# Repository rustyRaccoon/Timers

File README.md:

# Timers
 Vairous timer circuits, e.g. variable frequency, variable duty cycle, ...

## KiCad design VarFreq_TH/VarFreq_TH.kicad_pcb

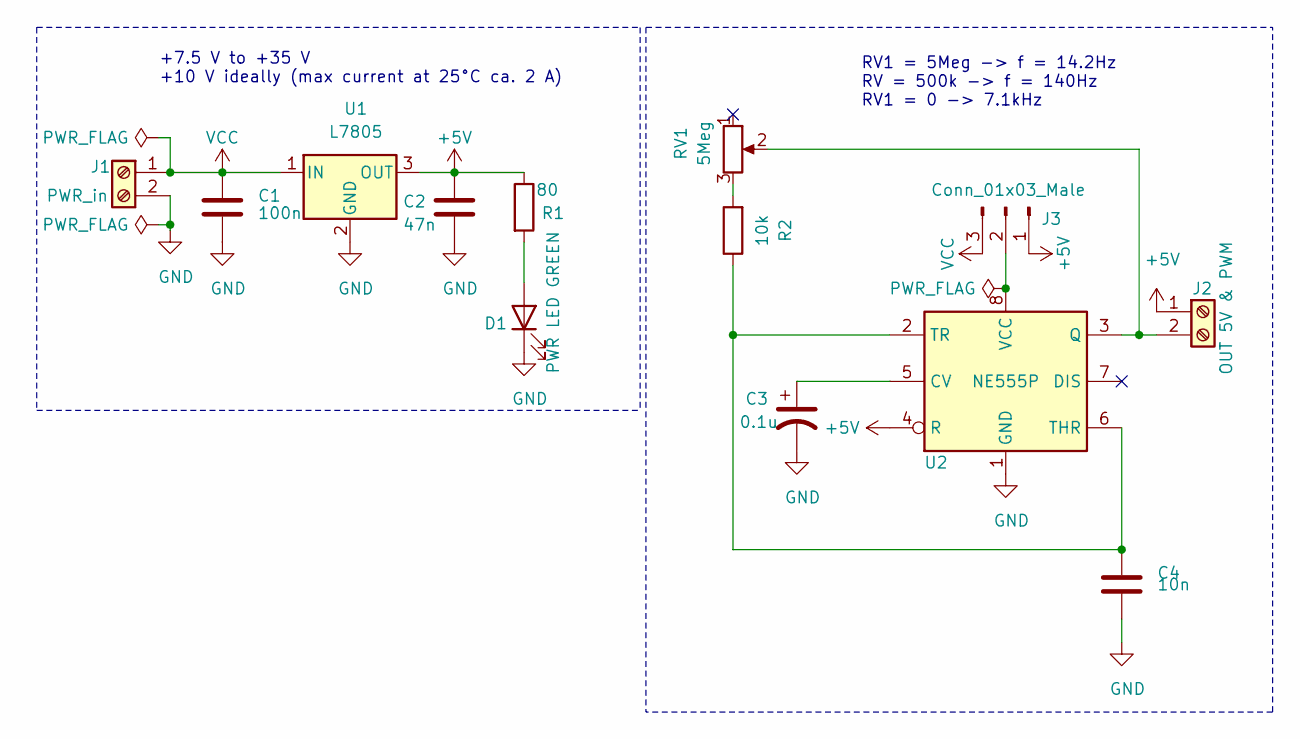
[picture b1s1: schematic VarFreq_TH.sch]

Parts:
C1: 100n; C_Radial_D6.3mm_H11.0mm_P2.50mm
C2: 47n; C_Radial_D6.3mm_H11.0mm_P2.50mm
C3: 0.1u; C_Disc_D4.3mm_W1.9mm_P5.00mm
C4: 10n; C_Disc_D4.3mm_W1.9mm_P5.00mm
D1: PWR LED GREEN; LED_D3.0mm
J1: PWR_in; TerminalBlock_bornier-2_P5.08mm
J2: OUT 5V & PWM; TerminalBlock_bornier-2_P5.08mm
J3: Conn_01x03_Male; PinHeader_1x03_P2.54mm_Vertical
R1: 80; R_Axial_DIN0204_L3.6mm_D1.6mm_P5.08mm_Horizontal
R2: 10k; R_Axial_DIN0204_L3.6mm_D1.6mm_P5.08mm_Horizontal
RV1: 5Meg; Potentiometer_Bourns_3296W_Vertical
U1: L7805; TO-220-3_Horizontal_TabDown
U2: NE555P; DIP-8_W7.62mm

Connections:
+5V: C2.1, J2.1, J3.1, R1.1, U1.3 (OUT), U2.4 (R)
GND: C1.2, C2.2, C3.2, C4.2, D1.1 (K), J1.2, U1.2 (GND), U2.1 (GND)
unnamed: C3.1, U2.5 (CV)
unnamed: C4.1, R2.1, U2.2 (TR), U2.6 (THR)
unnamed: D1.2 (A), R1.2
unnamed: J2.2, RV1.2, U2.3 (Q)
unnamed: J3.2, U2.8 (VCC)
unnamed: R2.2, RV1.3
VCC: C1.1, J1.1, J3.3, U1.1 (IN)

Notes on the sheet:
+7.5 V to +35 V +10 V ideally (max current at 25°C ca. 2 A)
RV1 = 5Meg -> f = 14.2Hz RV = 500k -> f = 140Hz RV1 = 0 -> 7.1kHz

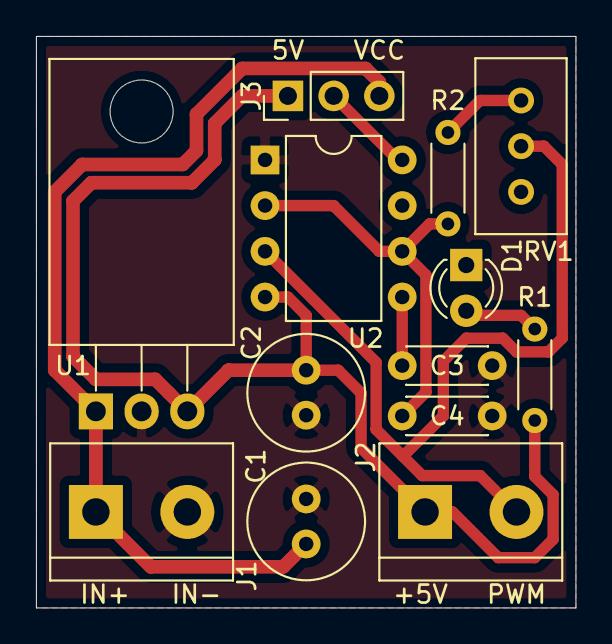
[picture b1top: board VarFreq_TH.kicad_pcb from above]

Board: 2 copper layers, 30.0 x 31.8 mm, 13 parts (0 on the bottom side), 9 nets.

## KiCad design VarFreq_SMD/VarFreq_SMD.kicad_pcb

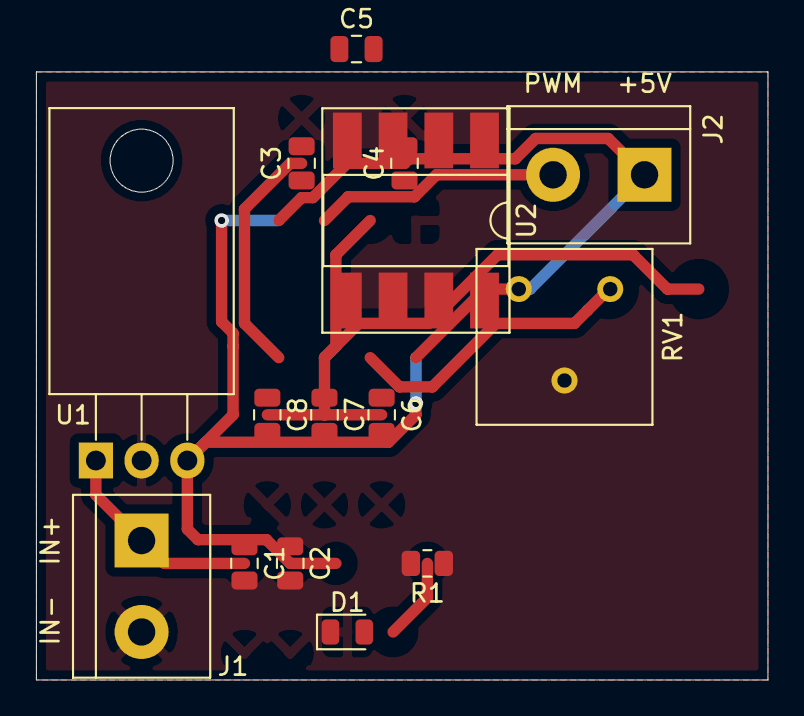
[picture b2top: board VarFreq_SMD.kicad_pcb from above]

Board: 2 copper layers, 40.6 x 33.8 mm, 15 parts (0 on the bottom side), 8 nets.

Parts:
C1, C7, C8: 100n; C_0805_2012Metric
C2: 47n; C_0805_2012Metric
C3: 0.1u; C_0805_2012Metric
C4: 0.01u; C_0805_2012Metric
C5, C6: 10n; C_0805_2012Metric
D1: PWR LED GREEN; LED_0805_2012Metric
J1: PWR_in; TerminalBlock_bornier-2_P5.08mm
J2: OUT 5V & PWM; TerminalBlock_bornier-2_P5.08mm
R1: R; R_0805_2012Metric
RV1: 10k; Potentiometer_Bourns_3386F_Vertical
U1: L7805; TO-220-3_Horizontal_TabDown
U2: NE555P; DIP-8_W8.89mm_SMDSocket_LongPads

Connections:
+5V: C2.1, C4.1, J2.1, R1.2, RV1.1, U1.3, U2.4, U2.8
GND: C1.2, C2.2, C3.2, C4.2, C5.2, C6.2, C7.2, C8.2, D1.1, J1.2, U1.2, U2.1
unnamed: C1.1, J1.1, U1.1
unnamed: C3.1, U2.5
unnamed: C5.1, C6.1, C7.1, C8.1, RV1.3, U2.2, U2.6
unnamed: D1.2, R1.1
unnamed: J2.2, U2.3
unnamed: RV1.2, U2.7
